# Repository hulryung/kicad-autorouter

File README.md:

# KiCad Autorouter

Route a placed PCB without leaving KiCad. Autorouter adds a toolbar button
with a built-in router, signal-integrity settings and an optional AI assistant.
The built-in router runs locally using KiCad's board model; no external routing
service or AI account is required.

**Current release:** [0.5.6 — testing / pre-release](https://github.com/hulryung/kicad-autorouter/releases/tag/v0.5.6)

**KiCad:** 9 and 10 · **License:** [MIT](LICENSE)

## What is implemented

| Area | Capabilities |
| --- | --- |
| Routing | Multi-layer A* search, rip-up and reroute, fine-pitch pad escapes, neck-down, short direct connections and a finer retry pass for unfinished nets. |
| Existing boards | Route remaining connections, route selected items or schematic sheets, or explicitly remove existing tracks first. Optional movement of existing unlocked copper through rip-up and reroute. |
| Board rules | Net-class and board minimum sizes, local clearances, keepouts, board edges, selectable copper layers and preferred directions. |
| Differential pairs | Coupled routes, pair layer changes, via swaps and single-ended end connections where needed, with exceptions reported in the log. |
| Ground and power | Plane-net detection, pad fanout, power ties, via stitching, zone refill and repair of isolated copper after routing. |
| Signal integrity | Stackup-based width estimates, impedance classes, length groups, routing priority, fabrication presets and KiCad tuning patterns. |
| AI assistance | Natural-language routing and edits, DRC feedback, board images, review requests, and iterative scoring and improvement through the Codex CLI. |
| Board setup | A check of Board Setup and the project's net classes before routing (outline, minimums, fabrication rules, net class patterns that match no net, pairs and power nets left in Default, pre-defined sizes, unfilled zones) with fixes to tick and apply. |
| Workflow | Live routing display, cancellation, undo through KiCad, persistent options, a pre-flight check before each run, per-board design intent and job logs. |

### New in 0.5.6

- No track or via is placed under an opening drawn on a solder mask layer
  (a logo, an exposed strip), unless the opening sits over that net's own
  pad or pour. KiCad's DRC reported such openings as bridging two nets: 44
  errors on the StickHub demo board, none now.
- An IC pin's track runs straight on past its pad before it turns, 0.3 mm
  more than before when the lane is free, as a designer fans out a QFP. On
  a TQFP board the straight run went 0.46 -> 0.64 mm (the designer's:
  0.95 mm) and pins leaving under the chip 41 -> 35 %.
- [Routing policies](docs/routing-policies.md) lists the layout conventions
  the router follows and how each was checked; `scripts/conventions.py`
  measures them on any routed board.

### New in 0.5.5

- A route that ended at the edge of its net's pour could come apart when
  another net routed in the same run cut that edge strip, and was still
  reported as routed. Pours are now refilled and checked after routing, and
  such a net is routed again to its pads.
- Isolated-copper repair only acts on pads that sit in a cut-off piece of
  their own pour. It had also added vias and stubs to pads no pour reaches,
  including on nets left out of the run. Planes joined through thermal
  through-hole pads are found, and repair vias keep clear of copper
  drawings and of keepouts over their whole pad.
- Half-done routes off the straight line between their pads are finished
  from the old track's end instead of redrawn pad to pad. Joins land on the
  old track's end point, and tails buried in other copper are removed. On
  the CM5 board with every third segment deleted (1807 mm), new copper went
  2261 -> 1941 mm and dangling-track warnings 88 -> 55.
- Reading a board with large connected copper pieces is faster (19.9 -> 4.6 s
  with 2000 vias in one pour).

### New in 0.5.4

- Boards with routes left half done: the router now starts and ends new
  copper on the board's own unfinished tracks, instead of routing pad to pad
  again on top of them and leaving the old pieces open. On the CM5 board
  with every third segment of each net deleted, unconnected items went
  121 -> 0 and copper drawn over the old tracks 271 -> 82 mm (mostly joins).
- A pad outside its net's pour is joined to the pour's edge rather than to
  a pad inside it with a track across the fill.

### New in 0.5.3

- A piece of a pour cut off from the rest of its net, with only its own pads
  in it, is tied back after routing: a short stub and a via down to the
  net's connected fill, placed where the copper and DRC's clearances leave
  room. On the CM5 board a signal routed round two GND pads of a resistor
  and a capacitor left them on such an island with the board's own rules.

### New in 0.5.2

- Dialog and AI-assistant runs get the same copper clean-up as the
  command-line pipeline: vias that join nothing are removed with their
  stubs, tiny off-angle joins are snapped and power rails are widened.
- Junctions are welded into shared end points: a route that ended inside a
  via off its centre or in the middle of another track now meets it at an
  end point, so KiCad no longer flags dangling ends and Select Connection
  (U) follows it. Copper is no longer drawn twice at such joins.
- Rip-up reaches a pin walled in by routes over its own room past the exit
  (HUB_nOC2 / HUB_nOC4 at a USB hub QFN were left open with the board's own
  clearance rules).
- Power widening respects a mounting hole's own clearance.

### New in 0.5.1

- Routing from the dialog is no longer throttled by macOS App Nap when KiCad's
  window is hidden or behind another app: on the four-layer CM5 board a run
  went from 1438 s to 511 s and finishes instead of hitting the time limit.
- In the dialog, later passes may move the plane vias the job itself placed,
  as the command-line pipeline already did.

### New in 0.5.0

- **Codex routing search:** **Score and improve** in the AI assistant (and
  `scripts/route-with-codex.py`) runs guarded experiments on a project copy:
  Codex proposes a routing change, the plugin applies it, re-runs KiCad DRC and
  has Codex score the result; only verified improvements are applied to the
  open board, together at the end. Codex also gets correctly scaled images of
  every copper layer. See [Codex routing search](#codex-routing-search).

### New in 0.4.0

- **Board setup tab:** checks Board Setup and the project's net classes before
  routing and applies the fixes you tick; a pre-flight check runs before each
  routing job.
- **Differential pairs:** pad entries turn toward the coupled run and follow
  the pad's own stub; pairs through flow-through TVS parts start from the twin
  pins facing onward; loose-end finishes no longer cross; pairs facing each
  other across a dense connector row fan outward; skew meanders go where the
  two lines are already apart; pairs outside an impedance class still get
  their P/N skew matched. Pair exceptions name the leg they apply to.
- **Power and ground:** power rails are widened after routing, up to 0.5 mm,
  wherever clearance allows (fine-pitch parts keep routing width); QFN
  exposed pads get a 2x2 via array and their GND pins join the pad directly.
- **Clean-up:** tiny off-angle joins are snapped, vias that join nothing are
  removed, and a via that only joins two tracks on one layer becomes a track.
- **Benchmarking:** `scripts/rubric.py` scores a benchmark with a fixed rubric
  (measured criteria plus the median of reviewer judgements), so results are
  repeatable.

## Installation

### Plugin and Content Manager

1. Open **Plugin and Content Manager** from KiCad's main project-manager window.
2. Open **Manage…**, add a repository, and paste:

   ```text
   https://raw.githubusercontent.com/hulryung/kicad-autorouter-pcm/main/repository.json
   ```

3. Select **KiCad Autorouter Repository**, choose **Autorouter**, click
   **Install**, then **Apply Pending Changes**.
4. Restart KiCad. Open a board in the PCB editor and click **Autorouter** on
   the toolbar, or use **Tools → External Plugins → Autorouter**.

PCM provides subsequent updates. To remove the plugin, use its **Installed**
tab; settings and job logs remain in the [data folder](#data-folder).

### Install from a ZIP

Download `kicad-autorouter-0.5.6.zip` from the
[release page](https://github.com/hulryung/kicad-autorouter/releases/tag/v0.5.6),
then choose **Plugin and Content Manager → Install from File…** and restart
KiCad. The release and PCM repositories distribute the same ZIP.

### Requirements and compatibility

- **KiCad 9 or 10**, using its `pcbnew` Python action-plugin API. KiCad 11 is
  not supported by this release; an IPC port is future work.
- The built-in router uses KiCad's bundled Python environment.
- The optional AI assistant requires an installed, authenticated `codex` CLI.
  DRC feedback uses `kicad-cli`.
- The plugin has macOS, Windows and Linux paths. The 0.5.6 release was tested
  on **macOS with KiCad 10.0.7**; that is the verified release environment.

### 한국어 설치 요약

KiCad 메인 창의 **플러그인 및 콘텐츠 관리자 → 관리…**에서 위 PCM 주소를
추가하세요. **Autorouter → 설치 → 변경 사항 적용** 후 KiCad를 재시작하면
PCB 편집기 툴바 또는 **도구 → 외부 플러그인**에서 실행할 수 있습니다.
KiCad 9/10을 지원하며, 기본 자동배선에는 AI 계정이 필요하지 않습니다.

## First routing run

1. Open a saved PCB with connected nets, placed footprints, a board outline,
   copper layers and design rules. Autorouter routes the placement you provide.
2. Open **Autorouter**. The default is to keep existing tracks and route the
   remaining connections. Removing existing tracks is an explicit per-run choice.
3. Set the routing scope, layers and sizes. If particular nets should use
   pours, enter their names or patterns, such as `GND,GND1,*_PLANE`, in
   **Nets to leave unrouted** and configure their zones.
4. Open **Board setup**: pick the board house's fabrication rules, read the
   check, tick the fixes you want and click **Apply ticked fixes**. The tab
   title counts the errors and warnings left.
5. Set any impedance or length constraints on **Signal integrity**, then click
   **Route**. Route runs the same check first: it offers to apply the chosen
   fabrication rules and stops on errors (such as a missing outline) unless you
   route anyway. Tracks appear as connections are found; the log reports progress,
   pair exceptions, retry passes and unfinished connections.
6. Inspect the result and run KiCad's DRC. Review any uncoupled pair ends and
   unmet length targets before treating the board as finished.

The default grid is **0.1 mm**, the search budget is **400,000 expansions per
connection**, and the routing time limit is **10 minutes** (`0` disables it).
The limit bounds the routing searches; pour finishing and length tuning can
continue afterwards, so it is not a strict wall-clock deadline for the dialog.
**Cancel** stops the run with partial work visible.

Board edits participate in KiCad's action-plugin undo. An optional subsequent
**Update All Tuning Patterns** operation has its own undo step. Saved settings,
design-intent files and written project rules are separate from copper undo.

### Dialog tabs

| Tab | Controls |
| --- | --- |
| **Routing** | Grid, via cost, search budget, time limit, track/via sizes, retries, coupled pairs, fanout, stitching, plane nets, existing copper, scope and zone refill. |
| **Board setup** | Fabrication rules preset, the board and project check, details per item, **Check again** and **Apply ticked fixes**. |
| **Signal integrity** | Stackup, impedance classes, pair limits, length groups, tuning options, routing order, **Compute sizes** and **Write to KiCad**. |
| **Layers & nets** | Routable copper layers, preferred horizontal/vertical directions and net classes to skip. |
| **AI assistant** | Request, model, round limit, DRC feedback, **Ask the assistant**, **Review current routing** and **Score and improve**. |

### Route part of a board

Choose **Selected items** after selecting footprints, pads, tracks or vias in
the editor. Footprint selections include connections touching those parts;
selected tracks and vias include their nets. Alternatively, choose
**Schematic sheets** and tick the sheets to route. Copper outside the routing
scope remains part of the obstacle model.

**Move existing tracks** allows eligible unlocked copper to be ripped up and
rerouted to make space. It is not KiCad's interactive push-and-shove engine;
locked copper remains fixed.

## Use with LCSC Manager

[LCSC Manager](https://github.com/hulryung/kicad-lcsc-manager) imports component
symbols, footprints and 3D models. Install both plugins in KiCad **9 or 10** by
adding the Autorouter PCM URL above and the LCSC Manager repository:

```text
https://raw.githubusercontent.com/hulryung/kicad-lcsc-manager/main/repository.json
```

The workflow is:

1. Import components with LCSC Manager.
2. Connect the schematic and update the PCB from it.
3. Place footprints and configure the outline, stackup, zones and design rules.
4. Run Autorouter, then inspect routing and DRC results.

The plugins work through the KiCad project; no direct plugin-to-plugin
connection is required. This is a shared workflow, not a bundled integration
or a claim of an end-to-end LCSC import/routing acceptance test.

한국어: 두 플러그인을 각각 설치한 뒤 **LCSC 부품 가져오기 → 회로 연결 →
PCB 배치·규칙 설정 → 자동배선 → DRC 검토** 순서로 사용하면 됩니다.

## Routing behavior

### Sizes, obstacles and escapes

Track widths, clearances, via diameters and drills come from the effective net
classes, with board minimums applied. Local clearance overrides, copper
obstacles, keepouts and board-edge clearance are included in extraction.
Automatic width selection considers existing copper and power-net pad sizes;
net-class, editor-selected and fixed sizes are also available.

The router creates pad escape lanes, protects fine-pitch via sites and uses
short direct links where they fit. Multi-layer A* routes the remaining
connections, with rip-up and reroute when paths conflict. A retry pass uses a
finer grid and can try both escape directions for stubborn pads. Through-via
clearance checks use the via footprint across copper layers.

### Differential pairs

Pairs can be identified from net names and design intent. Coupled routing uses
pair width and gap, with supported layer transitions and via swaps. If an end
cannot accommodate coupled tracks, the router can retain the coupled middle
and finish that end separately. Short pairs or pairs without a feasible coupled
route can fall back to separate routing. The log identifies these exceptions;
connectivity alone does not establish pair quality.

### Ground, power and copper islands

Plane-net detection identifies nets whose pours cover their pads. The pipeline
can place early pad-to-plane fanout, route signals, retry unfinished
connections, then add remaining fanout, power ties and stitching. With stitching
enabled, it refills and checks for isolated copper after those passes, adding
repair connections where feasible. Plane landing checks distinguish connected
copper components rather than treating every filled island as a valid ground
or power connection.

Filled zones are refilled around new copper. The router uses through vias;
blind and buried vias are not implemented.

## Board setup check

The **Board setup** tab reads Board Setup and the saved project file and lists
what keeps the router, the DRC or KiCad's interactive router from using the
right sizes. Fixes only add or raise; nothing the designer set is lowered or
removed.

| Check | Fix |
| --- | --- |
| No closed outline on Edge.Cuts (error) | Explained only: draw the outline. |
| Net class via, drill, track or clearance below the Constraints minimums (error) | Raise the class values to the minimums. |
| Board rules below the chosen fabrication preset | Raise them and write the hole rules to the `.kicad_dru`. |
| Copper-to-edge clearance under 0.2 mm (no preset chosen) | Set it to 0.3 mm. |
| Net class patterns that match no net, typically a stale sheet path (`/USB2*` for global `USB2_P`) | Add the corrected pattern beside the old one. |
| Differential pairs, found by name, in Default | Assign them to an existing class named for their impedance (90R for USB, 100R for Ethernet). |
| Power nets at the Default width | Opt in: create a **Power** class (0.4 mm tracks) and assign them. |
| Net class sizes missing from Pre-defined Sizes | Add them, so the editor's drop-downs offer them. |
| Copper zones not filled | Fill all zones. |
| No physical stackup on a multilayer board | Explained only: set it, or pick a template on Signal integrity. |

Board Setup changes are not on KiCad's undo list. They reach the `.kicad_pro`
when the board is saved. Pattern checks read the saved project file, so save
after editing net classes in Board Setup before checking again.

## Signal integrity and fabrication settings

Design intent is saved beside the board as **`<board>.autorouter.json`**.
The [examples](examples) show the same format used by the benchmarks.

- **Stackup:** use the board stackup or bundled JLCPCB 2-, 4- or 6-layer
  templates. Width calculations estimate microstrip/stripline impedance and
  differential coupling; they are not a field solver or a fabrication guarantee.
- **Impedance classes:** match nets by name patterns and specify single-ended
  or differential targets, pair gap and skew. Presets cover USB, Ethernet,
  LVDS/MIPI/HDMI, CAN/RS-485, RF and DDR; review their patterns and targets for
  the actual interface.
- **Length groups:** set a target and tolerance for groups such as memory
  lanes, QSPI, RGMII and SDIO. A zero target uses the longest member. Tuning
  adds meanders where room is available and reports the resulting lengths.
- **KiCad tuning patterns:** optionally hand generated meanders to KiCad's
  native tuning-pattern engine for updates and subsequent manual adjustment.
- **Routing order:** reorder differential pairs, memory, high-speed nets,
  clocks, routed power and other signals. Higher-priority protected routes
  constrain later rip-up searches.
- **Fabrication presets** (chosen on **Board setup**): bundled JLCPCB 2-, 4-
  and 6-layer rule templates raise board and net-class constraints while
  preserving stricter existing values. They are applied when you confirm, from
  the check or before a run, never silently. Check them against the fabrication service selected for your order.
- **Write to KiCad:** write calculated net classes and DRC rules, including
  per-layer width, pair gap/skew and length constraints, into the project.

Arbitrary conditional track-width and via-size rules in `.kicad_dru` are not
fully interpreted by the router. Final KiCad DRC remains necessary. Length,
skew and impedance targets may remain unmet when geometry leaves insufficient
room; inspect the reported results.

## Optional AI assistant

The **AI assistant** tab uses the Codex CLI to propose structured actions.
Each round supplies board context, routing results, a rendered board image
when available, and optional KiCad DRC feedback. Replies are checked against
an action schema and executed by the plugin.

| Mode | Behavior |
| --- | --- |
| **Ask the assistant** | Apply a natural-language routing or editing request over a bounded number of rounds. |
| **Review current routing** | Ask the model for note-only feedback on the current routing. |
| **Score and improve** | Test routing experiments on isolated board copies, re-score with all copper-layer images and mandatory DRC, and apply only the best verified result at the end. |

Actions include changing options; routing nets, selections or sheets with
layer/width/avoid-area hints; adding or removing tracks and vias; moving
footprints or nearby copper; resizing copper; inspecting a region; and
refilling zones. The assistant can also leave notes or ask a question and stop.

In **Ask the assistant** mode, with verification enabled, edits are measured
before and after. Supported
add/move/resize edits that increase the DRC violation count are rolled back
unless the action explicitly sets `force`. This is not a transaction-wide
rollback guarantee: route and removal actions are not in that rollback set.

The CLI is launched with a read-only sandbox in the job folder; the plugin
performs the returned board edits. Using AI supplies board context and images
to the configured AI service. Prompts, replies, images and review results are
kept locally in the job folder. The built-in router works without this feature.

## Codex routing search

The **Score and improve** button and the CLI use the same guarded
search loop: Codex proposes a routing experiment, the plugin applies it to a
project copy, re-runs KiCad DRC, and asks Codex to score the resulting board.
Rejected attempts never replace the best accepted board. This replaces the
earlier in-place reviewer shipped in releases 0.3.0 and 0.4.0.

### From the PCB editor

1. Install the plugin, open your PCB and set routing and SI options.
2. Open **AI assistant**, enter a request, and set **Rounds** (1–10; default 3).
   Leave **Model** blank to use your Codex CLI configuration.
3. Click **Score and improve**. Each experiment starts from the best accepted
   board and uses previous rejection reasons to guide the next proposal.
4. Review the final score and applied-improvement count. Use **Open data folder**
   to inspect `jobs/<time>-<board>-optimize/search/optimization.json` and its
   candidates, then inspect the applied board and save it in KiCad.

In the dialog, **Rounds** limits the number of experiments. The open board's
copper stays unchanged during the search; accepted tracks, vias, arcs and tuning
groups are applied together at the end. Placement, pad assignments and locked
copper are protected. **Cancel** leaves the open board's copper unchanged and
keeps the saved candidates in the data folder. DRC is mandatory for this mode,
including when the optional DRC checkbox for the ordinary assistant is off.

For scoped search requests, name nets or schematic sheets explicitly. Editor
selection is not passed into this mode. Footprint movement is supported by
**Ask the assistant**, but is rejected by **Score and improve**.

### From the command line

```bash
/path/to/kicad-python scripts/route-with-codex.py /path/to/board.kicad_pcb \
  --out /path/to/new-output-folder --attempts 8 --patience 4 \
  --request "Finish connectivity, then reduce detours and unnecessary vias."
```

Use KiCad's Python, an authenticated Codex CLI and `kicad-cli`. `--model` can
select the CLI model; omitting it uses the CLI configuration. `--time-limit`
sets minutes per native routing action, not a deadline for the complete search.

| Option | Default | Purpose |
| --- | --- | --- |
| `--out` | Required | Separate output directory for this run. |
| `--attempts` | `8` | Maximum number of proposed experiments. |
| `--patience` | `4` | Stop after this many consecutive rejected or failed experiments; acceptance resets the count. |
| `--min-gain` | `1` | Minimum score increase required for acceptance. |
| `--time-limit` | `10` | Minutes per native routing action; `0` disables that routing limit. |
| `--model` | CLI configuration | Model used for proposals and reviews. |
| `--codex` | Auto-detected | Explicit path to the Codex executable. |
| `--request` | Route completely, then improve quality | Routing objective supplied to Codex. |

### Acceptance and saved results

Each candidate must increase the reviewer score by `--min-gain` (default 1),
introduce no new DRC errors, and leave no additional unconnected items. It must
also improve connectivity, remove an existing DRC error, or reduce measured
copper cost (track length in mm plus 2 per via) by more than 0.1 without increasing non-octilinear
straight segments. A higher model score alone is insufficient. These checks
are routing acceptance criteria, not proof of signal-integrity compliance.

The loop retains the best PCB and its project/rule/intent sidecars, with the
path and all attempt decisions in `optimization.json`. Each attempt retains its
context, images, CLI logs and Codex replies for inspection. The input PCB is unchanged.
Use a new output directory for each run. A run stops at its attempt limit,
patience limit, a request for missing information, or no further executable
proposal; inspect its status rather than interpreting every stop as completion.

The report records `best_board`, `initial_score`, `best_score`, `best_metrics`,
`best_drc` and the actions, acceptance decision and reason for each attempt.
The best board may be the original copy if no candidate passes the checks.

| Report status | Meaning |
| --- | --- |
| `attempt_limit` | The experiment budget was exhausted. |
| `plateau` | The consecutive-failure limit was reached. |
| `no_proposal` | The assistant returned no executable board-edit proposal. |
| `needs_input` | The assistant asked a question; inspect the saved actions or dialog log. |
| `cancelled` / `failed` | The search was interrupted; a report retains the best result if initial assessment completed. |

## Validation and examples

### Codex search

Live Codex runs on macOS with KiCad 10.0.7 exercised both the dialog button and
the CLI:

| Case | Accepted reviewer scores | Final unconnected items | DRC result |
| --- | --- | --- | --- |
| Public OBD2 fixture, actual **Score and improve** button | 15 → 87 → 89 | 0 | No added errors; one existing invalid-outline error remained. |
| Already-routed four-layer CM5 reference, CLI | 78 → 79 | 0 | No added errors; four existing hole-clearance errors remained. |

The CM5 run reduced copper length from 5741.3 to 5740.8 mm with 435 vias and
stopped after four subsequent attempts failed acceptance. The dialog run
preserved the source file and open project while applying the accepted copper.
Scores are model judgments from individual runs, not reproducible benchmarks
or a guarantee that every run improves a board.

Automated tests cover score-only rejection, added DRC errors, connectivity
regressions, candidate isolation, cancellation, subprocess cleanup, copper-layer
rendering, and transfer of groups and tuning patterns. The desktop-enabled suite
passed; native PCB-editor Undo was not manually exercised for this new mode.

### Native router (0.4.0 and later)

For the **0.4.0 four-layer CM5 regression**, three deterministic search budgets
produced the following results:

| Work-rate setting (expansions/s) | 0.3.0: unconnected | 0.4.0: unconnected | Added physical / rule errors | Vias | Off-45 segments |
| --- | --- | --- | --- | --- | --- |
| 85,000 | 0 | 0 | 0 / 0 | 414 | 3 |
| 100,000 | 0 | 0 | 0 / 0 | 414 | 3 |
| 115,000 | 0 | 0 | 0 / 0 | 414 | 3 |

All three final runs produced the same geometry. Only pre-existing footprint
and text warnings of the reference board remained. On the fixed rubric
(`scripts/rubric.py`) the result scores 84.1, against 79.6 for the starting
point of this release cycle; the HUB_DN2 pair went from 0 % to 49 % coupled
and the +5 V rail from 0.2 mm to mostly 0.3–0.5 mm. These work-rate settings
control deterministic search budgets; they are not measured machine
throughput. This regression
establishes connectivity and absence of added errors on that board, not
fabrication readiness or complete signal-integrity compliance.

The offline suite, KiCad end-to-end tests and GUI smoke test passed on macOS
with KiCad 10.0.7 for the release. Live AI service tests were excluded. The
public [OBD2 fixture test](tests/test_native_e2e.py) requires zero remaining
connections and no added DRC errors for its default fixture. The larger CM5
reference PCB is not distributed in this repository.

These earlier artwork examples illustrate the routing style; they are not
screenshots of the CM5 regression above:

| Original artwork | Autorouted example |
| --- | --- |
|  |  |

| Earlier LED routing | Improved pad escapes and direct links |
| --- | --- |
|  |  |

## Troubleshooting and logs

- **No toolbar button:** restart KiCad or refresh external plugins. Check
  **Preferences → PCB Editor → Action Plugins** and enable the toolbar button.
- **Package not compatible:** use KiCad 9 or 10; this release has no IPC build.
- **Some connections remain:** inspect the log and DRC, check scopes, skipped
  nets, layers and sizes, then consider a finer grid or a larger search budget.
  A finer grid increases runtime and memory use.
- **AI assistant unavailable:** check that an authenticated `codex` executable
  is discoverable by KiCad. Built-in routing remains available.
- **Need to inspect a run:** click **Open data folder**. A built-in run writes
  `jobs/<time>-<board>/dialog.log`; AI runs also retain context and responses.

### Data folder

| OS | Default path |
| --- | --- |
| macOS | `~/Library/Application Support/kicad-autorouter` |
| Windows | `%LOCALAPPDATA%\kicad-autorouter` |
| Linux | `$XDG_DATA_HOME/kicad-autorouter`, or `~/.local/share/kicad-autorouter` |

The folder contains `settings.json`, logs and jobs. The most recent 10 job
folders are retained. `KICAD_AUTOROUTER_HOME` overrides the location. Per-board
signal-integrity intent stays beside the PCB, separate from global settings.

## Development

```bash
git clone https://github.com/hulryung/kicad-autorouter
cd kicad-autorouter
./scripts/install-dev.sh
# Optional development reload on each invocation:
touch plugins/autorouter/.devreload
```

The helper links the plugin into existing KiCad 9/10 user scripting directories.
Do not load both a PCM installation and a development copy at the same time.
Use `./scripts/install-dev.sh --remove` to remove the development links.

### Source layout

```text
plugins/autorouter/
  plugin.py, dialog.py     action plugin, routing UI and live updates
  si_page.py              signal-integrity UI
  setup_page.py           board setup check UI
  settings.py             persistent user options
  engine/
    native/
      pipeline.py         multi-pass routing, pours and tuning orchestration
      extract.py          KiCad board -> routing problem
      grid.py, astar.py    occupancy grids and path search
      router.py           ordering, rip-up, pairs, fanout and stitching
      islands.py          connected copper components and island repair
      apply.py            paths -> KiCad copper
      tuning.py           length matching
      kicad_tuning.py     native KiCad tuning-pattern integration
      problem.py          shared routing data models
    si.py, stackup.py      design intent and impedance estimates
    fab.py                fabrication-rule presets
    board_setup.py        board and project checks and their fixes
    ai/                   context, CLI bridge, actions, rendering, review and guarded optimization
    options.py            routing options
    session.py, paths.py   board helpers, jobs and data locations
```

### Tests

```bash
# Offline tests; tests needing pcbnew/wx skip when unavailable:
python3 scripts/run-tests.py

# macOS: also run tests requiring KiCad's Python:
/Applications/KiCad/KiCad.app/Contents/Frameworks/Python.framework/Versions/Current/bin/python3 scripts/run-tests.py

# GUI smoke test: run in a desktop session with KiCad's Python:
KICAD_AUTOROUTER_GUI_TESTS=1 /path/to/kicad-python scripts/run-tests.py dialog_smoke

# Guarded Codex search and dialog tests (scripted model; no AI account needed):
KICAD_AUTOROUTER_GUI_TESTS=1 /path/to/kicad-python scripts/run-tests.py ai_

# Route a supplied board and collect results:
/path/to/kicad-python tests/test_native_e2e.py path/to/board.kicad_pcb --skip GND --out /tmp/routed

# Live AI test: explicitly opt in, with an authenticated Codex CLI:
KICAD_AUTOROUTER_AI_LIVE=1 /path/to/kicad-python tests/test_ai_live.py
```

Replace `/path/to/kicad-python` with a Python interpreter that can import
KiCad's `pcbnew` module. Tests cover routing grids, escapes, via clearance,
plane landing, island repair, SI settings, fake-CLI AI behavior, packaging and
the native pipeline. A skipped test is not evidence that its integration passed.

### Benchmark and improvement tools

`scripts/improve_bench.py` routes a copy of a supplied reference board and
writes connectivity, DRC, geometry and optional design-intent metrics, plus
comparison images. `scripts/improve-loop.py` uses Claude Code to evaluate
those results, modify the router in an isolated Git worktree, and retain
changes only when its acceptance checks pass. Claude Code is a developer tool
for this workflow, not a runtime dependency of the plugin.

Supply your own reference PCB; the developer's default board path is not
included in the repository:

```bash
python3 scripts/improve-loop.py \
  --reference /path/to/reference.kicad_pcb \
  --skip GND,GND1,GND2 --rounds 3 --time-limit 10 \
  --work-rates 85000,100000,115000 --intent /path/to/board.autorouter.json
```

With `--time-limit`, work-rate settings test multiple deterministic search
budgets. Use `--intent none` to disable design intent. Results, transcripts,
patches and the report stay under `.improve/<time>/`; kept changes remain on
an `improve/<time>` branch for review, rather than being merged automatically.

### Build and publish

```bash
python3 scripts/build-package.py
python3 scripts/publish-pcm.py --no-push
```

The builder writes a versioned PCM ZIP under `release/`, prints a JSON
checksum/size summary, excludes development/cache files and checks version consistency.
The second command prepares and commits the separate PCM checkout locally.
After reviewing it, `python3 scripts/publish-pcm.py` pushes the catalogue and
package. GitHub Releases are published separately; attach the same tested ZIP.

## Current limits and future work

- KiCad 11 requires an IPC implementation; the current plugin uses SWIG.
- Routing uses a uniform grid and through vias. Dense layouts can require
  smaller pitches, longer searches or manual completion.
- Pair coupling and length matching are best-effort and expose exceptions;
  they do not replace electrical review.
- Broader cross-platform validation, blind/buried vias and richer routing
  constraints remain future work.

## License

[MIT](LICENSE). The source and installable package are publicly available.

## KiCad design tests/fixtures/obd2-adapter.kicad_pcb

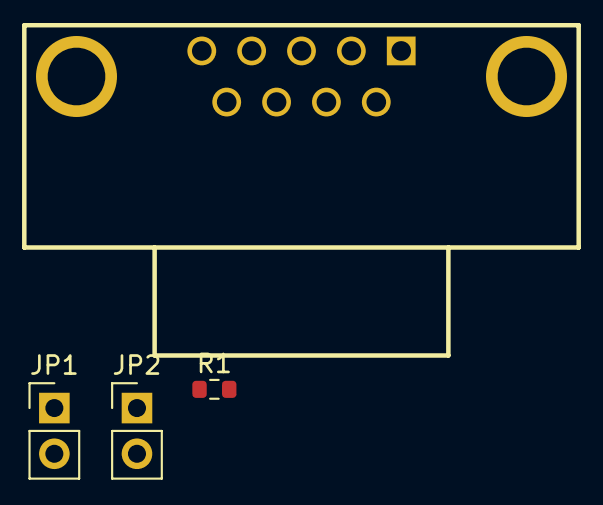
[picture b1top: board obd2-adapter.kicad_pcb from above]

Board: 2 copper layers, 4 parts (0 on the bottom side), 5 nets, no tracks yet.

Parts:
J1: DE9_Socket; CONN-TH_D-SUB-DR-9PCM-CB
JP1: TERM; PinHeader_1x02_P2.54mm_Vertical
JP2: VBAT; PinHeader_1x02_P2.54mm_Vertical
R1: 120; R_0603_1608Metric

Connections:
/CANH: J1.7, JP1.1
/CANL: J1.2, R1.2
/TERM_H: JP1.2, R1.1
/VBAT_SW: J1.9, JP2.2
GND: J1.3, J1.6
